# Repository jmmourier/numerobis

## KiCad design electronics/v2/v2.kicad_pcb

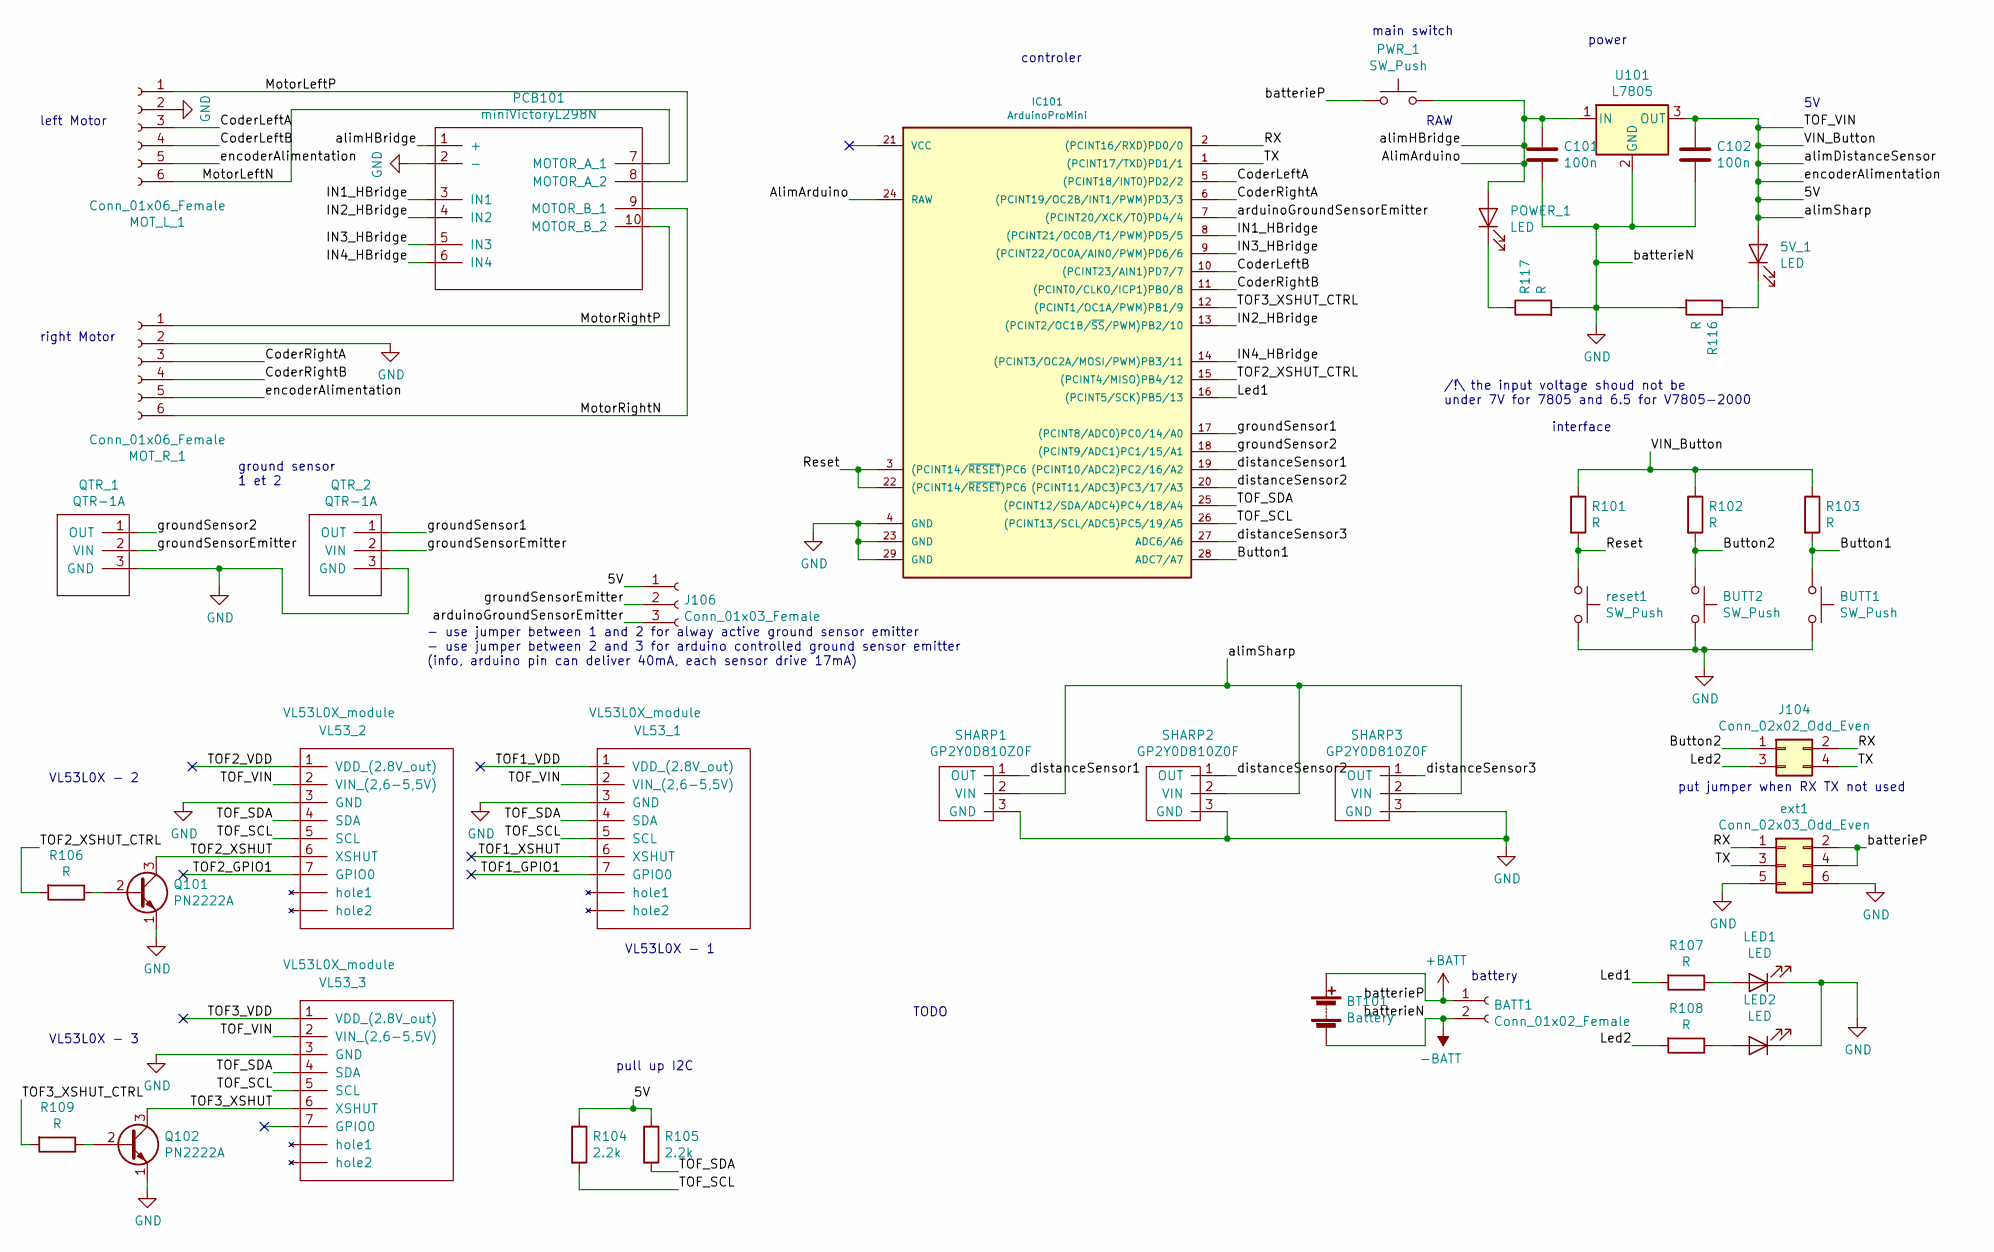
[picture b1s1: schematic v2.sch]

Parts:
5V_1: LED; LED_D5.0mm
BATT1: Conn_01x02_Female; Molex_KK-6410-02_02x2.54mm_Straight
BT101: Battery
BUTT1, BUTT2: SW_Push; SW_PUSH_6mm_h4.3mm
C101, C102: 100n; CP_Radial_D5.0mm_P2.50mm
IC101: ArduinoProMini; pro_mini
J104: Conn_02x02_Odd_Even; Pin_Header_Straight_2x02_Pitch2.54mm
J106: Conn_01x03_Female; Pin_Header_Straight_1x03_Pitch2.54mm
LED1, LED2: LED; LED_D5.0mm
MOT_L_1: Conn_01x06_Female; Molex_KK-6410-06_06x2.54mm_Straight
MOT_R_1: Conn_01x06_Female; Molex_KK-6410-06_06x2.54mm_Straight
PCB101: miniVictoryL298N
POWER_1: LED; LED_D5.0mm
PWR_1: SW_Push; SW_CuK_OS102011MA1QN1_SPDT_Angled
Q101, Q102: PN2222A; TO-92_Inline_Wide
QTR_1, QTR_2: QTR-1A; Pin_Header_Angled_1x03_Pitch2.54mm
R101, R102, R103, R106, R107, R108, R109, R116, R117: R; R_Axial_DIN0207_L6.3mm_D2.5mm_P10.16mm_Horizontal
R104, R105: 2.2k; R_Axial_DIN0207_L6.3mm_D2.5mm_P10.16mm_Horizontal
SHARP1, SHARP2, SHARP3: GP2Y0D810Z0F; Pin_Header_Straight_1x03_Pitch2.54mm
U101: L7805; TO-220-3_Vertical
VL53_1, VL53_2, VL53_3: VL53L0X_module; Pin_Header_Straight_1x07_Pitch2.54mm
ext1: Conn_02x03_Odd_Even; Pin_Header_Straight_2x03_Pitch2.54mm
reset1: SW_Push; SW_PUSH_6mm_h4.3mm

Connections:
+BATT: BATT1.1, BT101.1 (+), PWR_1.1, ext1.2, ext1.4
-BATT: BATT1.2, BT101.2 (-), BUTT1.2, BUTT2.2, C101.2, C102.2, IC101.4 (GND), IC101.23 (GND), IC101.29 (GND), LED1.1 (K), LED2.1 (K), MOT_L_1.2, MOT_R_1.2, PCB101.2 (-), Q101.1 (E), Q102.1 (E), QTR_1.3 (GND), QTR_2.3 (GND), R116.2, R117.2, SHARP1.3 (GND), SHARP2.3 (GND), SHARP3.3 (GND), U101.2 (GND), VL53_1.3 (GND), VL53_2.3 (GND), VL53_3.3 (GND), ext1.5, ext1.6, reset1.2
/5V: 5V_1.2 (A), C102.1, J106.1, MOT_L_1.5, MOT_R_1.5, R101.1, R102.1, R103.1, R104.1, R105.1, SHARP1.2 (VIN), SHARP2.2 (VIN), SHARP3.2 (VIN), U101.3 (OUT), VL53_1.2 (VIN_(2,6-5,5V)), VL53_2.2 (VIN_(2,6-5,5V)), VL53_3.2 (VIN_(2,6-5,5V))
/AlimArduino: C101.1, IC101.24 (RAW), PCB101.1 (+), POWER_1.2 (A), PWR_1.2, U101.1 (IN)
/Button1: BUTT1.1, IC101.28 (ADC7/A7), R103.2
/Button2: BUTT2.1, J104.1, R102.2
/CoderLeftA: IC101.5 ((PCINT18/INT0)PD2/2), MOT_L_1.3
/CoderLeftB: IC101.10 ((PCINT23/AIN1)PD7/7), MOT_L_1.4
/CoderRightA: IC101.6 ((PCINT19/OC2B/INT1/PWM)PD3/3), MOT_R_1.3
/CoderRightB: IC101.11 ((PCINT0/CLKO/ICP1)PB0/8), MOT_R_1.4
/IN1_HBridge: IC101.8 ((PCINT21/OC0B/T1/PWM)PD5/5), PCB101.3 (IN1)
/IN2_HBridge: IC101.13 ((PCINT2/OC1B/~SS~/PWM)PB2/10), PCB101.4 (IN2)
/IN3_HBridge: IC101.9 ((PCINT22/OC0A/AIN0/PWM)PD6/6), PCB101.5 (IN3)
/IN4_HBridge: IC101.14 ((PCINT3/OC2A/MOSI/PWM)PB3/11), PCB101.6 (IN4)
/Led1: IC101.16 ((PCINT5/SCK)PB5/13), R107.2
/Led2: J104.3, R108.2
/MotorLeftN: MOT_L_1.6, PCB101.7 (MOTOR_A_1)
/MotorLeftP: MOT_L_1.1, PCB101.8 (MOTOR_A_2)
/MotorRightN: MOT_R_1.6, PCB101.9 (MOTOR_B_1)
/MotorRightP: MOT_R_1.1, PCB101.10 (MOTOR_B_2)
/RX: IC101.2 ((PCINT16/RXD)PD0/0), J104.2, ext1.1
/Reset: IC101.3 ((PCINT14/~RESET~)PC6), IC101.22 ((PCINT14/~RESET~)PC6), R101.2, reset1.1
/TOF1_GPIO1: VL53_1.7 (GPIO0)
/TOF1_VDD: VL53_1.1 (VDD_(2.8V_out))
/TOF1_XSHUT: VL53_1.6 (XSHUT)
/TOF2_GPIO1: VL53_2.7 (GPIO0)
/TOF2_VDD: VL53_2.1 (VDD_(2.8V_out))
/TOF2_XSHUT: Q101.3 (C), VL53_2.6 (XSHUT)
/TOF2_XSHUT_CTRL: IC101.15 ((PCINT4/MISO)PB4/12), R106.2
/TOF3_VDD: VL53_3.1 (VDD_(2.8V_out))
/TOF3_XSHUT: Q102.3 (C), VL53_3.6 (XSHUT)
/TOF3_XSHUT_CTRL: IC101.12 ((PCINT1/OC1A/PWM)PB1/9), R109.2
/TOF_SCL: IC101.26 ((PCINT13/SCL/ADC5)PC5/19/A5), R104.2, VL53_1.5 (SCL), VL53_2.5 (SCL), VL53_3.5 (SCL)
/TOF_SDA: IC101.25 ((PCINT12/SDA/ADC4)PC4/18/A4), R105.2, VL53_1.4 (SDA), VL53_2.4 (SDA), VL53_3.4 (SDA)
/TX: IC101.1 ((PCINT17/TXD)PD1/1), J104.4, ext1.3
/arduinoGroundSensorEmitter: IC101.7 ((PCINT20/XCK/T0)PD4/4), J106.3
/distanceSensor1: IC101.19 ((PCINT10/ADC2)PC2/16/A2), SHARP1.1 (OUT)
/distanceSensor2: IC101.20 ((PCINT11/ADC3)PC3/17/A3), SHARP2.1 (OUT)
/distanceSensor3: IC101.27 (ADC6/A6), SHARP3.1 (OUT)
/groundSensor1: IC101.17 ((PCINT8/ADC0)PC0/14/A0), QTR_2.1 (OUT)
/groundSensor2: IC101.18 ((PCINT9/ADC1)PC1/15/A1), QTR_1.1 (OUT)
/groundSensorEmitter: J106.2, QTR_1.2 (VIN), QTR_2.2 (VIN)
unnamed: 5V_1.1 (K), R116.1
unnamed: LED1.2 (A), R107.1
unnamed: LED2.2 (A), R108.1
unnamed: POWER_1.1 (K), R117.1
unnamed: Q101.2 (B), R106.1
unnamed: Q102.2 (B), R109.1

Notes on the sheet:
left Motor
right Motor
power
controler
VL53L0X - 1
ground sensor 1 et 2
VL53L0X - 2
interface
TODO
battery
RAW
pull up I2C
/!\ the input voltage shoud not be under 7V for 7805 and 6.5 for V7805-2000
put jumper when RX TX not used
- use jumper between 1 and 2 for alway active ground sensor emitter - use jumper between 2 and 3 for arduino controlled ground sensor emitter (info, arduino pin can deliver 40mA, each sensor drive 17mA)
main switch
VL53L0X - 3

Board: 2 copper layers, 40 parts (0 on the bottom side), 42 nets, no tracks yet.

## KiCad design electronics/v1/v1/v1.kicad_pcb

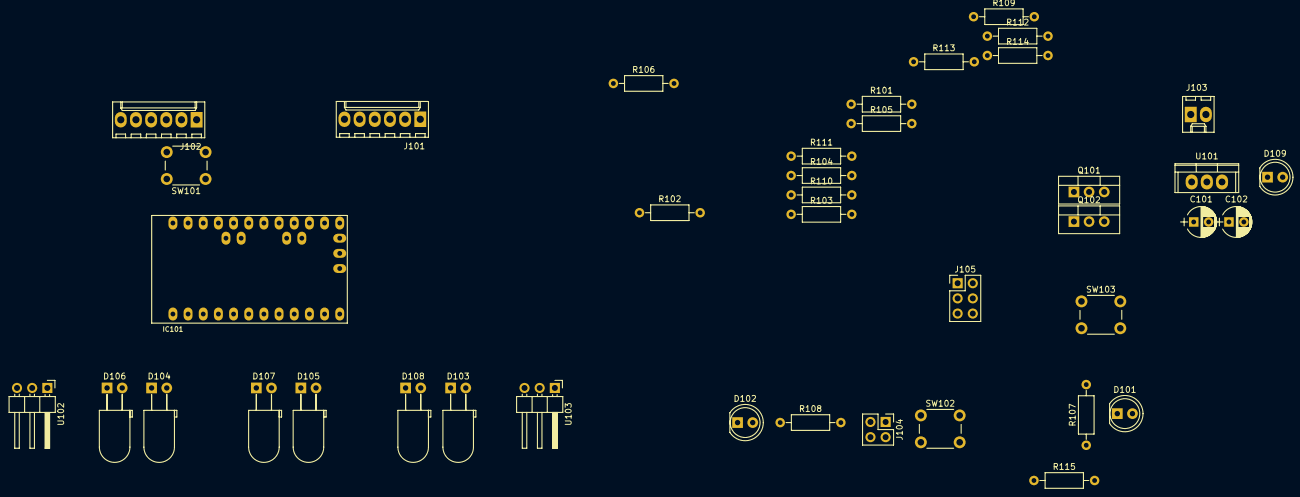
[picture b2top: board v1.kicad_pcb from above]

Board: 2 copper layers, 40 parts (0 on the bottom side), 32 nets, no tracks yet.

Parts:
C101, C102: 100n; CP_Radial_D5.0mm_P2.50mm
D101, D102: LED; LED_D5.0mm_FlatTop
D103, D104, D105: LED; LED_D5.0mm_Horizontal_O3.81mm_Z3.0mm
D106, D107, D108: D_Photo; LED_D5.0mm_Horizontal_O3.81mm_Z3.0mm
D109: LED; LED_D5.0mm
IC101: ArduinoProMini; pro_mini
J101, J102: Conn_01x06_Female; Molex_KK-6410-06_06x2.54mm_Straight
J103: Conn_01x02_Female; Molex_KK-6410-02_02x2.54mm_Straight
J104: Conn_02x02_Odd_Even; Pin_Header_Straight_2x02_Pitch2.54mm
J105: Conn_02x03_Odd_Even; Pin_Header_Straight_2x03_Pitch2.54mm
Q101, Q102: TIP122; TO-220-3_Vertical
R101, R102, R103, R106, R107, R108, R109, R110, R111, R112, R113, R114, R115: R; R_Axial_DIN0207_L6.3mm_D2.5mm_P10.16mm_Horizontal
R104, R105: 2.2k; R_Axial_DIN0207_L6.3mm_D2.5mm_P10.16mm_Horizontal
SW101, SW102, SW103: SW_Push; SW_PUSH_6mm_h4.3mm
U101: L7805; TO-220
U102, U103: QTR-1A; Pin_Header_Angled_1x03_Pitch2.54mm

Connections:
/5V: C102.1, D109.2, J101.4, J102.4, R101.1, R102.1, R103.1, R104.1, R105.1, R109.1, R110.1, R111.1, R112.1, R113.1, R114.1, U101.3
/AlimArduino: C101.1, IC101.24, J103.1, J105.2, J105.4, U101.1
/Button1: IC101.28, R103.2, SW103.1
/Button2: J104.1, R102.2, SW102.1
/CoderLeftA: IC101.5, J101.3
/CoderLeftB: IC101.10, J101.2
/CoderRightA: IC101.6, J102.3
/CoderRightB: IC101.11, J102.2
/Led1: IC101.16, R107.2
/Led2: J104.3, R108.2
/RX: IC101.2, J104.2, J105.1
/Reset: IC101.3, IC101.22, R101.2, SW101.1
/TOF2_XSHUT_CTRL: IC101.15, R106.1
/TOF_SCL: IC101.26, R104.2
/TOF_SDA: IC101.25, R105.2
/TX: IC101.1, J104.4, J105.3
/distanceSensor1: D108.1, IC101.19, R114.2
/distanceSensor2: D107.1, IC101.20, R113.2
/distanceSensor3: D106.1, IC101.27, R112.2
/distanceSensorEmitter: IC101.12, R115.1
/groundSensor1: IC101.17, U103.1
/groundSensor2: IC101.18, U102.1
/groundSensorEmitter: IC101.7, U102.2, U103.2
GND: C101.2, C102.2, D101.1, D102.1, D106.2, D107.2, D108.2, IC101.4, IC101.23, IC101.29, J101.1, J102.1, J103.2, J105.5, J105.6, Q101.3, Q102.3, SW101.2, SW102.2, SW103.2, U101.2, U102.3, U103.3
unnamed: D101.2, R107.1
unnamed: D102.2, R108.1
unnamed: D103.1, D104.1, D105.1, Q102.2
unnamed: D103.2, R109.2
unnamed: D104.2, R110.2
unnamed: D105.2, R111.2
unnamed: Q101.1, R106.2
unnamed: Q102.1, R115.2

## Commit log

2019-01-31 [Common][Elec][Docs] first commit with all electronics and quick presentation
2019-01-31 Set theme jekyll-theme-minimal
2019-01-31 Update README.md
    [Docs] Format text
2019-01-31 Set theme jekyll-theme-midnight
2019-02-08 add mechanical part, first test not working, need to be redisign
2019-02-08 update files for 3D and resistor values
2019-02-08 unit test project ok
2019-02-14 add preparation file (use of class)
2019-03-16 add soft for loop control motor and strategy night before competition
2019-03-16 add forgetted mechanical files, stronger version for motor holder and shell of the robot
2019-03-16 add lib vl53l0x and I2C non blocking for investigating the probleme with left tof
